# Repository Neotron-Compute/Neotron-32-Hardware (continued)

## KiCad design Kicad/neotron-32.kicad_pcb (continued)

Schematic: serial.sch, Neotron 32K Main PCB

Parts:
C901, C902: 100n; C_Disc_D3.0mm_W2.0mm_P2.50mm; mpn K104K15X7RF5TL2
C903, C904, C905: 100n; C_Disc_D3.0mm_W2.0mm_P2.50mm; mpn K474Z20Y5VE5TL2
J901: Conn_02x05; IDC-Header_2x05_P2.54mm_Vertical; mpn 302-S101
U901: ICL3232CPZMAX; DIP-16_W7.62mm; mpn ICL3232CPZ;ED16DT

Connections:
/PB0_U1RX: U901.12 (R1OUT); also elsewhere on the board
/PB1_U1TX: U901.11 (T1IN); also elsewhere on the board
/PC4_U1RTS: U901.10 (T2IN); also elsewhere on the board
/PC5_U1CTS: U901.9 (R2OUT); also elsewhere on the board
/RS-232 Serial Port/RS232_CTS_IN: J901.8, U901.8 (R2IN)
/RS-232 Serial Port/RS232_RTS_OUT: J901.7, U901.7 (T2OUT)
/RS-232 Serial Port/RS232_RX_IN: J901.2, U901.13 (R1IN)
/RS-232 Serial Port/RS232_TX_OUT: J901.3, U901.14 (T1OUT)
GND: C901.1, C904.1, J901.5, U901.15 (GND); also elsewhere on the board
unnamed: C902.1, U901.3 (C1-)
unnamed: C902.2, U901.1 (C1+)
unnamed: C903.1, U901.4 (C2+)
unnamed: C903.2, U901.5 (C2-)
unnamed: C904.2, U901.6 (VS-)
unnamed: C905.2, U901.2 (VS+)

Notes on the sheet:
Header for IDC to DE9 Ribbon. Wired DTE.
This chip is a 3.3V capable version of the MAX232 RS-232 level shifter. The port is wired DTE (i.e. as if this was an IBM PC, rather than as a modem). We only have a five-wire RS-232 interface, missing the Ring Input, Data Set Ready, Data Terminal Ready and Carrier Detect pins. If you want a proper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

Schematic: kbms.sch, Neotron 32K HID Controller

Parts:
C1002, C1003, C1004: 100n; C_Disc_D3.0mm_W2.0mm_P2.50mm; mpn K104K15X7RF5TL2
D1001, D1002: LED; LED_D3.0mm
FB1001: 100R; LairdTech_28C0236-0JW-10
J1002: 1x3 UART Debug Header; PinHeader_1x03_P2.54mm_Vertical
J1003: Double-mini-DIN-6; Double_mini-DIN_6; mpn KMDGX-6S-6S-S4N.
J1004: AVR-ISP-6; PinHeader_2x03_P2.54mm_Vertical
R1004, R1005: 1k; R_Axial_DIN0207_L6.3mm_D2.5mm_P10.16mm_Horizontal
R1006, R1008: 6.81k 1%; R_Axial_DIN0207_L6.3mm_D2.5mm_P10.16mm_Horizontal
R1007, R1009: 1k 1%; R_Axial_DIN0207_L6.3mm_D2.5mm_P10.16mm_Horizontal
R1010: 10k; R_Axial_DIN0207_L6.3mm_D2.5mm_P10.16mm_Horizontal
SW1001: SW_Push_DPDT_ON_MO; PHB2UEETS1A; mpn PHB2UOATS1A
U1002: ATmega328P-PU; DIP-28_W7.62mm

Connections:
+5V: C1003.1, FB1001.2, J1003.4, J1003.10, J1004.2 (VCC), R1004.1, R1005.1, R1006.2, U1002.7 (VCC); also elsewhere on the board
/Keyboard and Mouse/AT_MISO: J1004.1 (MISO), U1002.18 (PB4)
/Keyboard and Mouse/AT_MOSI: J1004.4 (MOSI), U1002.17 (PB3)
/Keyboard and Mouse/AT_SCK: J1004.3 (SCK), U1002.19 (PB5)
/Keyboard and Mouse/KB_CLK: J1003.5, U1002.4 (PD2)
/Keyboard and Mouse/KB_DAT: J1003.1, U1002.6 (PD4)
/Keyboard and Mouse/MON_3V3: R1008.1, R1009.2, U1002.24 (PC1)
/Keyboard and Mouse/MON_5V0: R1006.1, R1007.2, U1002.23 (PC0)
/Keyboard and Mouse/MS_CLK: J1003.11, U1002.5 (PD3)
/Keyboard and Mouse/MS_DAT: J1003.7, U1002.11 (PD5)
/Keyboard and Mouse/UART_RX: J1002.1, U1002.2 (PD0)
/Keyboard and Mouse/UART_TX: J1002.2, U1002.3 (PD1)
/Keyboard and Mouse/~AT_RESET: J1004.5 (~RST), U1002.1 (~RESET~/PC6)
/PA6_I2C_SCL: U1002.28 (PC5); also elsewhere on the board
/PA7_I2C_SDA: U1002.27 (PC4); also elsewhere on the board
/~PF4_HID_IRQ: U1002.26 (PC3); also elsewhere on the board
/~POWER_ON: R1010.1, U1002.25 (PC2); also elsewhere on the board
/~RESET: U1002.12 (PD6); also elsewhere on the board
GND: C1002.1, C1003.2, C1004.2, J1002.3, J1003.3, J1003.9, J1004.6 (GND), R1007.1, R1009.1, SW1001.2 (B), SW1001.5 (B), U1002.8 (GND), U1002.22 (GND); also elsewhere on the board
unnamed: C1002.2, U1002.21 (AREF)
unnamed: C1004.1, FB1001.1, U1002.20 (AVCC)
unnamed: D1001.1 (K), U1002.15 (PB1)
unnamed: D1001.2 (A), R1004.2
unnamed: D1002.1 (K), U1002.16 (PB2)
unnamed: D1002.2 (A), R1005.2
unnamed: R1010.2, SW1001.3 (C), SW1001.6 (C), U1002.13 (PD7)

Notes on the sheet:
The AtMega 328 acts as the interface to the 5V PS/2 Keyboard and PS/2 Mouse. It does this by implementing the Microsoft "HID over I2C" standard. The AtMega also handles the power button. When off, a short push will ground ~POWER_EN~, which will activate the PSU. Once the AtMega has booted it sets P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
Voltage Monitoring: measure against 1.1V band-gap ref (5.0V * 1000) / (6810 + 1000) = 640 mV (3.3V * 1000) / (6810 + 1000) = 422 mV
Power Button: Tap to turn on/off Hold to hard power off (if main MCU has crashed)
LEDs - Power and Fault
AtMega328 Pin Functions

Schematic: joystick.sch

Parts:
C1101: 100n; C_Disc_D3.0mm_W2.0mm_P2.50mm; mpn K104K15X7RF5TL2
J1101: 2x3 Header; PinHeader_2x03_P2.54mm_Vertical
R1101, R1102, R1103: 10k; R_Axial_DIN0207_L6.3mm_D2.5mm_P10.16mm_Horizontal
U1101: MCP23017_SP; DIP-28_W7.62mm

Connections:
+5V: C1101.1, J1101.1, J1101.3, J1101.5, U1101.9 (VDD); also elsewhere on the board
/Joystick/JS1_A_B: U1101.5 (GPB4); also elsewhere on the board
/Joystick/JS1_DOWN: U1101.2 (GPB1); also elsewhere on the board
/Joystick/JS1_LEFT: U1101.3 (GPB2); also elsewhere on the board
/Joystick/JS1_RIGHT: U1101.4 (GPB3); also elsewhere on the board
/Joystick/JS1_SELECT: U1101.7 (GPB6); also elsewhere on the board
/Joystick/JS1_START_C: U1101.6 (GPB5); also elsewhere on the board
/Joystick/JS1_UP: U1101.1 (GPB0); also elsewhere on the board
/Joystick/JS2_A_B: U1101.25 (GPA4); also elsewhere on the board
/Joystick/JS2_DOWN: U1101.22 (GPA1); also elsewhere on the board
/Joystick/JS2_LEFT: U1101.23 (GPA2); also elsewhere on the board
/Joystick/JS2_RIGHT: U1101.24 (GPA3); also elsewhere on the board
/Joystick/JS2_SELECT: U1101.27 (GPA6); also elsewhere on the board
/Joystick/JS2_START_C: U1101.26 (GPA5); also elsewhere on the board
/Joystick/JS2_UP: U1101.21 (GPA0); also elsewhere on the board
/PA6_I2C_SCL: U1101.12 (SCK); also elsewhere on the board
/PA7_I2C_SDA: U1101.13 (SDA); also elsewhere on the board
GND: C1101.2, R1101.1, R1102.1, R1103.1, U1101.10 (VSS); also elsewhere on the board
unnamed: J1101.2, R1101.2, U1101.17 (A2)
unnamed: J1101.4, R1102.2, U1101.16 (A1)
unnamed: J1101.6, R1103.2, U1101.15 (A0)

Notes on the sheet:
Address Select
The MCP23017 handles the two Atari/SEGA controller ports. A SEGA Master System pad is much like an Atari joystick, but a Mega Drive (or Genesis) 3-button pad will return both Left and Right active (low) when read. As this is impossible on a standard Joystick, this indicates it is a SEGA pad and tha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

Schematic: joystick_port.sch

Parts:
J1101: DE9 Male; DSUB-9_Male_Horizontal_P2.77x2.84mm_EdgePinOffset14.56mm_Ho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; mpn 5747467-2

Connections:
+5V: J1101.1, J1101.3, J1101.5; also elsewhere on the board
unnamed 118: J1101.2; also elsewhere on the board
unnamed 119: J1101.4; also elsewhere on the board
unnamed 120: J1101.6; also elsewhere on the board

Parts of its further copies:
J1201, J1301: DE9 Male; DSUB-9_Male_Horizontal_P2.77x2.84mm_EdgePinOffset14.56mm_Ho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; mpn 5747467-2

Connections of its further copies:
+5V: J1201.5, J1301.5; also elsewhere on the board
/Joystick/JS1_A_B: J1301.6; also elsewhere on the board
/Joystick/JS1_DOWN: J1301.2; also elsewhere on the board
/Joystick/JS1_LEFT: J1301.3; also elsewhere on the board
/Joystick/JS1_RIGHT: J1301.4; also elsewhere on the board
/Joystick/JS1_SELECT: J1301.7; also elsewhere on the board
/Joystick/JS1_START_C: J1301.9; also elsewhere on the board
/Joystick/JS1_UP: J1301.1; also elsewhere on the board
/Joystick/JS2_A_B: J1201.6; also elsewhere on the board
/Joystick/JS2_DOWN: J1201.2; also elsewhere on the board
/Joystick/JS2_LEFT: J1201.3; also elsewhere on the board
/Joystick/JS2_RIGHT: J1201.4; also elsewhere on the board
/Joystick/JS2_SELECT: J1201.7; also elsewhere on the board
/Joystick/JS2_START_C: J1201.9; also elsewhere on the board
/Joystick/JS2_UP: J1201.1; also elsewhere on the board
GND: J1201.8, J1301.8; also elsewhere on the board

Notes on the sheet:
Digital Atari/SEGA Compatible Joystick Port If LEFT and RIGHT read as GND, flip SELECT and read alternate set of pins (C, B, LEFT, RIGHT).

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
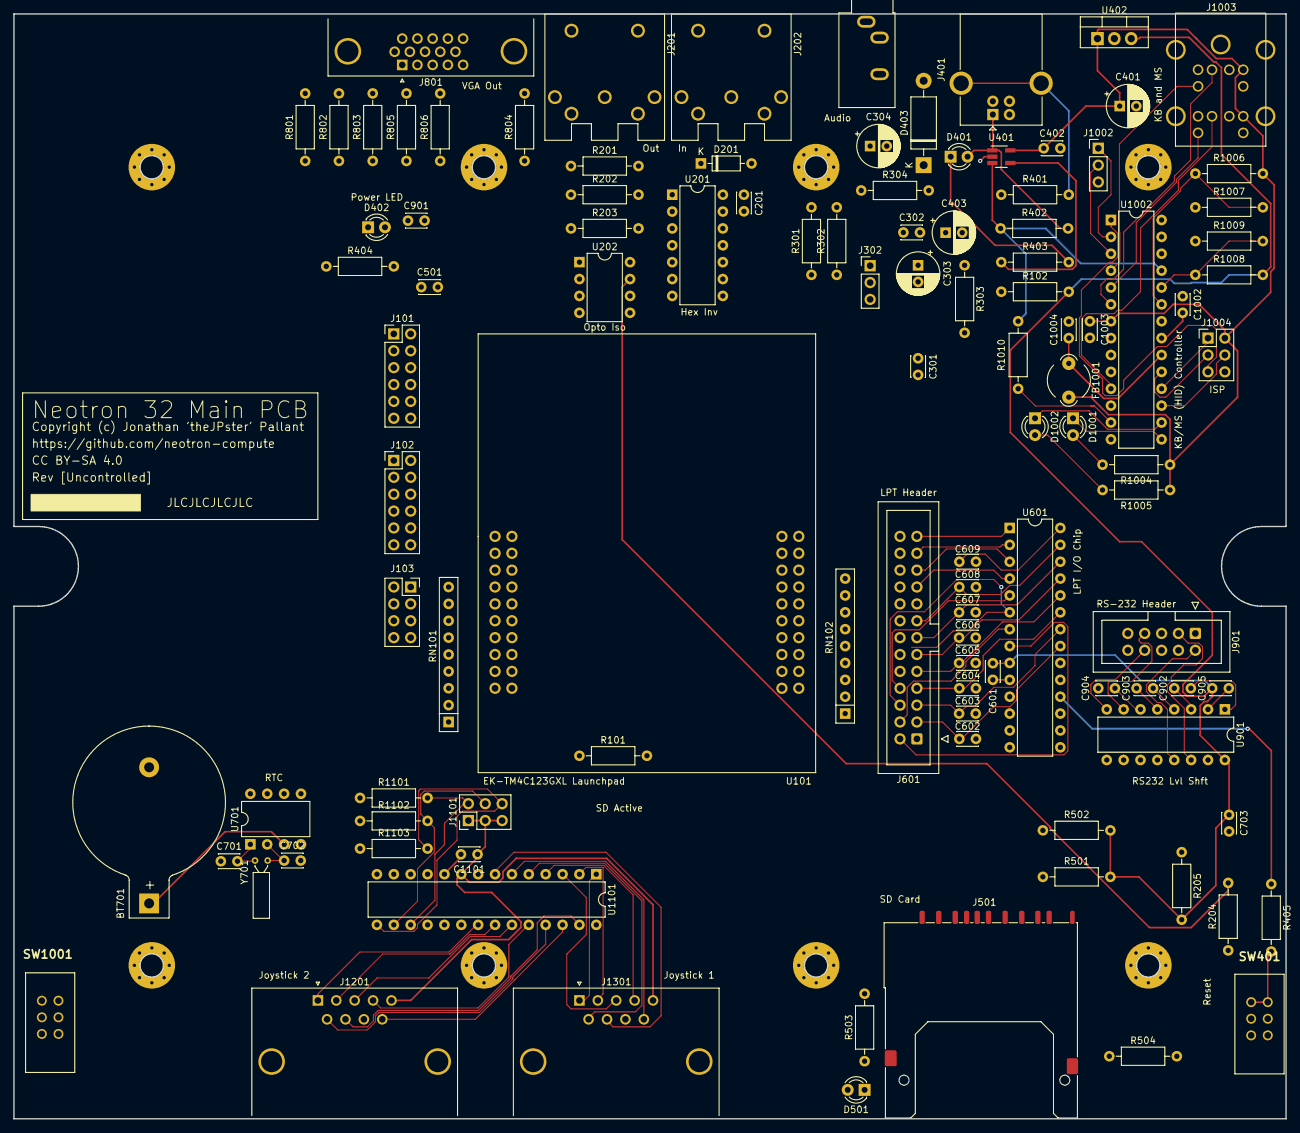
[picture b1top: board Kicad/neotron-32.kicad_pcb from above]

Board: 2 copper layers, 191.5 x 166.3 mm, 116 parts (0 on the bottom side), 130 nets.

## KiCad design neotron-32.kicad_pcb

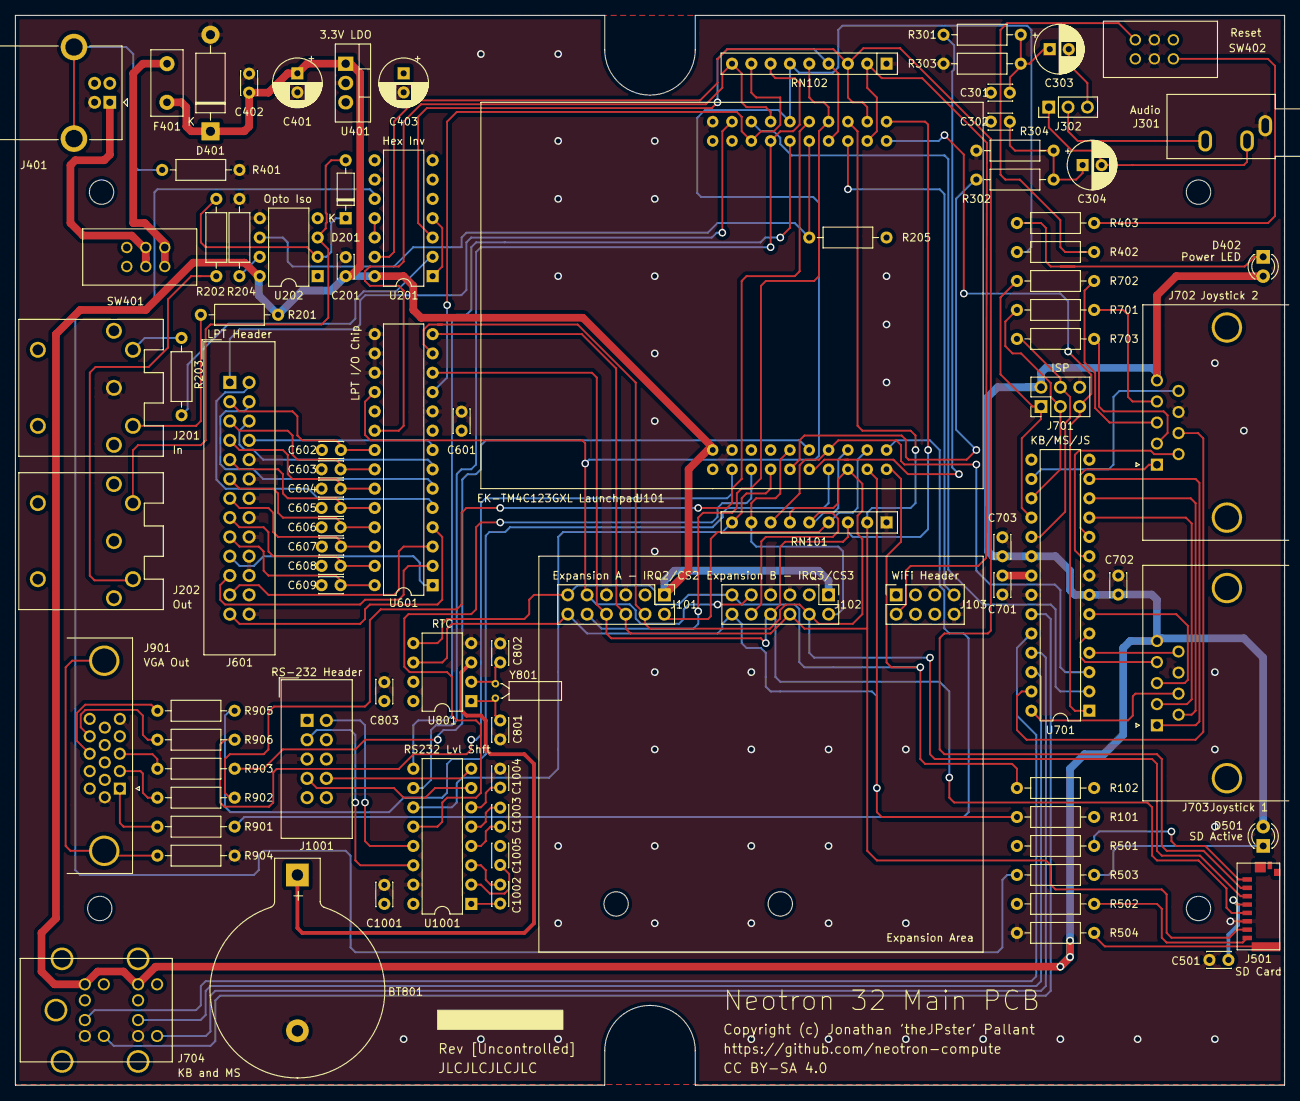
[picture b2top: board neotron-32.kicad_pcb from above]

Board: 4 copper layers, 166.9 x 140.7 mm, 97 parts (0 on the bottom side), 117 nets.

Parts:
BT801: CR2032; BatteryHolder_Keystone_103_1x20mm
C201, C402, C501, C601, C701, C702, C703, C803, C1001, C1002, C1003, C1004, C1005: 100n; C_Disc_D3.0mm_W2.0mm_P2.50mm
C301, C302: 33n; C_Disc_D3.0mm_W2.0mm_P2.50mm
C303, C304, C401: 10u; CP_Radial_D6.3mm_P2.50mm
C403: 47u; CP_Radial_D6.3mm_P2.50mm
C602, C603, C604, C605, C606, C607, C608, C609: 22n; C_Disc_D3.0mm_W2.0mm_P2.50mm
C801, C802: 6p; C_Disc_D3.0mm_W2.0mm_P2.50mm
D201: 1N4148; D_DO-35_SOD27_P7.62mm_Horizontal
D401: SA5.0A; D_DO-15_P12.70mm_Horizontal
D402, D501: Red LED; LED_D3.0mm
F401: 250mA PTC; Fuse_Littelfuse_395Series
H101, H102, H103, H104, H105, H106: MountingHole; MountingHole_3.2mm_M3
J101, J102: Conn_02x06; PinHeader_2x06_P2.54mm_Vertical
J103: Conn_02x04; PinSocket_2x04_P2.54mm_Vertical
J201, J202: DIN-5 180 degree; 5P180_DIN_Socket
J301: 3.5mm Audio Jack TRS; Jack_3.5mm_CUI_SJ1-3533NG_Horizontal
J302: Conn_01x03_Male; PinHeader_1x03_P2.54mm_Vertical
J401: USB_B; USB_B_OST_USB-B1HSxx_Horizontal
J501: micro SD Card; Molex_4730_2651
J601: Conn_02x13_Header; IDC-Header_2x13_P2.54mm_Vertical
J701: AVR-ISP-6; PinHeader_2x03_P2.54mm_Vertical
J702, J703: DE9 Male; DSUB-9_Male_Horizontal_P2.77x2.84mm_EdgePinOffset14.56mm_Ho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
J704: Double-mini-DIN-6; Double_mini-DIN_6
J901: DB15HD_Female; DSUB-15-HD_Female_Horizontal_P2.29x1.98mm_EdgePinOffset3.03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
J1001: Conn_02x05; IDC-Header_2x05_P2.54mm_Vertical
R101, R102, R701, R702, R703: 1k; R_Axial_DIN0207_L6.3mm_D2.5mm_P10.16mm_Horizontal
R201, R202, R203: 220; R_Axial_DIN0207_L6.3mm_D2.5mm_P10.16mm_Horizontal
R204: 10k; R_Axial_DIN0207_L6.3mm_D2.5mm_P10.16mm_Horizontal
R205: 470; R_Axial_DIN0207_L6.3mm_D2.5mm_P10.16mm_Horizontal
R301, R302: 270; R_Axial_DIN0207_L6.3mm_D2.5mm_P10.16mm_Horizontal
R303, R304: 150; R_Axial_DIN0207_L6.3mm_D2.5mm_P10.16mm_Horizontal
R401, R504, R904: DNF; R_Axial_DIN0207_L6.3mm_D2.5mm_P10.16mm_Horizontal
R402, R403, R503, R901, R902, R903, R905, R906: 330; R_Axial_DIN0207_L6.3mm_D2.5mm_P10.16mm_Horizontal
R501, R502: 47k; R_Axial_DIN0207_L6.3mm_D2.5mm_P10.16mm_Horizontal
RN101, RN102: 47k x 8; R_Array_SIP9
SW401: SW_Push_DPDT_ON_OFF; PHB2UEETS1A
SW402: SW_Push_DPDT_ON_MO; PHB2UEETS1A
U101: EK-TM4C123GXL; Launchpad_4x10
U201: 74LS14; DIP-14_W7.62mm
U202: 6N138; DIP-8_W7.62mm
U401: TC1262-33; TO-220-3_Vertical
U601: MCP23S17_SP; DIP-28_W7.62mm
U701: ATmega328-PU; DIP-28_W7.62mm
U801: MCP7940N-xP; DIP-8_W7.62mm
U1001: ICL3232CPZMAX; DIP-16_W7.62mm
Y801: 32,768 Hz; Crystal_C26-LF_D2.1mm_L6.5mm_Horizontal

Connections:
+3V3: C403.1, C501.1, C601.1, C803.1, C1001.2, C1005.1, J101.3, J102.3, J103.1, J501.4, R101.2, R102.2, R205.2, R501.2, R502.2, U401.3, U601.9, U801.8, U1001.16
+5V: C201.1, C401.1, C402.1, C702.1, C703.1, D401.1, D402.2, D501.2, F401.1, J101.1, J102.1, J701.2, J702.5, J703.5, J704.4, J704.10, R201.2, U101.3.1, U201.14, U202.8, U401.1, U701.7, U701.20
+BATT: BT801.1, U801.3
/Audio/LEFT_CHAN: C304.2, J301.T, J302.1
/Audio/RIGHT_CHAN: C303.2, J302.3
/Audio/RIGHT_SPKR: J301.R, J302.2
/Keyboard, Mouse and Joystick/AT_MISO: J701.1, R702.2, U701.18
/Keyboard, Mouse and Joystick/AT_MOSI: J701.4, R703.2, U701.19
/Keyboard, Mouse and Joystick/AT_SCK: J701.3, R701.2, U701.17
/Keyboard, Mouse and Joystick/A_B_JS1: J703.6, U701.12
/Keyboard, Mouse and Joystick/A_B_JS2: J702.6, U701.9
/Keyboard, Mouse and Joystick/DOWN_JS1: J703.2, U701.11
/Keyboard, Mouse and Joystick/DOWN_JS2: J702.2, R703.1
/Keyboard, Mouse and Joystick/KB_CLK: J704.5, U701.23
/Keyboard, Mouse and Joystick/KB_DAT: J704.1, U701.24
/Keyboard, Mouse and Joystick/LEFT_GND_JS1: J703.3, U701.6
/Keyboard, Mouse and Joystick/LEFT_GND_JS2: J702.3, R702.1
/Keyboard, Mouse and Joystick/MS_CLK: J704.11, U701.25
/Keyboard, Mouse and Joystick/MS_DAT: J704.7, U701.26
/Keyboard, Mouse and Joystick/RIGHT_GND_JS1: J703.4, U701.5
/Keyboard, Mouse and Joystick/RIGHT_GND_JS2: J702.4, R701.1
/Keyboard, Mouse and Joystick/SELECT_JS1: J703.7, U701.28
/Keyboard, Mouse and Joystick/SELECT_JS2: J702.7, U701.27
/Keyboard, Mouse and Joystick/START_C_JS1: J703.9, U701.4
/Keyboard, Mouse and Joystick/START_C_JS2: J702.9, U701.16
/Keyboard, Mouse and Joystick/UP_JS1: J703.1, U701.13
/Keyboard, Mouse and Joystick/UP_JS2: J702.1, U701.10
/PA2_SPI_CLK: J101.8, J102.8, J501.5, RN101.3, U101.2.10, U601.12
/PA4_SPI_MISO: J101.6, J102.6, J501.7, RN101.2, U101.2.8, U601.14
/PA5_SPI_MOSI: J101.4, J102.4, J501.3, RN101.6, U101.1.8, U601.13
/PA6_I2C_SCL: J101.12, J102.12, R101.1, U101.1.9, U801.6
/PA7_I2C_SDA: J101.11, J102.11, R102.1, U101.1.10, U801.5
/PB0_U1RX: U101.1.3, U1001.12
/PB1_U1TX: RN101.9, U101.1.4, U1001.11
/PB4_VGA_HSYNC: R905.1, U101.1.7
/PB5_VGA_VSYNC: R906.1, U101.1.2
/PB7_VGA_GREEN: R902.2, U101.2.6
/PC4_U1RTS: RN102.7, U101.4.4, U1001.10
/PC5_U1CTS: U101.4.5, U1001.9
/PC6_MIDI_IN: R205.1, U101.4.6, U202.6
/PC7_MIDI_OUT: RN102.4, U101.4.7, U201.3
/PD3_VGA_BLUE: R903.2, U101.3.6
/PD6_U2RX: J103.7, U101.4.8
/PD7_U2TX: J103.2, RN102.2, U101.4.9
/PE0_U7RX: U101.2.3, U701.2
/PE1_U7TX: RN101.7, U101.3.7, U701.3
/PE4_AUDIO_L: R302.2, U101.1.5
/PE5_AUDIO_R: R301.2, U101.1.6
/PF1_VGA_RED: R901.2, U101.3.10
/Parallel Printer/ACK: J601.19, U601.1
/Parallel Printer/D0: C602.2, J601.3, U601.21
/Parallel Printer/D1: C603.2, J601.5, U601.22
/Parallel Printer/D2: C604.2, J601.7, U601.23
/Parallel Printer/D3: C605.2, J601.9, U601.24
/Parallel Printer/D4: C606.2, J601.11, U601.25
/Parallel Printer/D5: C607.2, J601.13, U601.26
/Parallel Printer/D6: C608.2, J601.15, U601.27
/Parallel Printer/D7: C609.2, J601.17, U601.28
/Parallel Printer/ERROR: J601.4, U601.6
/Parallel Printer/POUT: J601.23, U601.3
/Parallel Printer/RESET: J601.6, U601.7
/Parallel Printer/SELECT: J601.25, U601.4
/Parallel Printer/~BUSY: J601.21, U601.2
/Parallel Printer/~LF: J601.2, U601.5
/Parallel Printer/~SELPRI: J601.8, U601.8
/Power/UNFUSED_5V: F401.2, SW401.3, SW401.6
/Power/VUSB: J401.1, SW401.2, SW401.5
/RS-232 Serial Port/RS232_CTS_IN: J1001.8, U1001.8
/RS-232 Serial Port/RS232_RTS_OUT: J1001.7, U1001.7
/RS-232 Serial Port/RS232_RX_IN: J1001.2, U1001.13
/RS-232 Serial Port/RS232_TX_OUT: J1001.3, U1001.14
/~PA3_SPI_CS0: J501.2, RN102.3, U101.2.9, U201.13
/~PB2_STROBE: J601.1, U101.2.2
/~PB3_SPI_CS1: RN102.8, U101.4.3, U601.11
/~PB6_SPI_CS2: J101.10, RN102.5, U101.2.7
/~PD2_IRQ3: J102.2, RN101.8, U101.3.5
/~PE2_SPI_CS3: J102.10, RN101.5, U101.3.8
/~PE3_IRQ2: J101.2, RN101.4, U101.3.9
/~PF0_IRQ1: RN102.9, U101.2.4, U601.20
/~PF4_AT_RESET: J701.5, U101.4.10, U701.1
/~RESET: J101.9, J102.9, R402.1, RN102.6, U101.2.5, U601.18
GND: BT801.2, C201.2, C301.1, C302.1, C401.2, C402.2, C403.2, C501.2, C601.2, C602.1, C603.1, C604.1, C605.1, C606.1, C607.1, C608.1, C609.1, C701.1, C702.2, C703.2, C801.1, C802.2, C803.2, C1001.1, C1004.1, D401.2, J101.5, J101.7, J102.5, J102.7, J103.8, J201.2, J301.S, J401.4, J501.6, J601.10, J601.12, J601.14, J601.16, J601.18, J601.20, J601.22, J601.24, J601.26, J701.6, J702.8, J703.8, J704.3, J704.9, J901.5, J901.6, J901.7, J901.8, J1001.5, R204.1, R303.2, R304.2, R401.1, R504.2, R904.1, RN101.1, RN102.1, SW402.2, SW402.5, U101.2.1, U101.3.2, U201.5, U201.7, U201.9, U202.5, U401.2, U601.10, U601.15, U601.16, U601.17, U701.8, U701.22, U801.4, U1001.15
unnamed: C301.2, C303.1, R301.1, R303.1
unnamed: C302.2, C304.1, R302.1, R304.1
unnamed: C701.2, U701.21
unnamed: C801.2, U801.1, Y801.1
unnamed: C802.1, U801.2, Y801.2
unnamed: C1002.1, U1001.3
unnamed: C1002.2, U1001.1
unnamed: C1003.1, U1001.4
unnamed: C1003.2, U1001.5
unnamed: C1004.2, U1001.6
unnamed: C1005.2, U1001.2
unnamed: D201.1, R202.1, U202.2
unnamed: D201.2, J202.5, U202.3
unnamed: D402.1, R403.1
unnamed: D501.1, R503.1
unnamed: J201.4, R201.1
unnamed: J201.5, R203.2
unnamed: J202.4, R202.2
unnamed: J401.5, R401.2
unnamed: J501.1, R501.1
unnamed: J501.8, R502.1
unnamed: J501.9, R504.1
unnamed: J901.0, R904.2
unnamed: J901.1, R901.1
unnamed: J901.2, R902.1
unnamed: J901.3, R903.1
unnamed: J901.13, R905.2
unnamed: J901.14, R906.2
unnamed: R203.1, U201.2
unnamed: R204.2, U202.7
unnamed: R402.2, SW402.3
unnamed: R403.2, SW402.4
unnamed: R503.2, U201.10
unnamed: U201.1, U201.4
unnamed: U201.11, U201.12

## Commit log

2019-11-10 Skeleton schematic.
2019-11-10 Add datasheets and example schematics.
2019-11-10 Add USB Library user guide.
2019-12-08 Update hardware specs in README.
2019-12-09 Adding sub-sheets
2019-12-09 Ignore backup PCB files.
2019-12-09 Added some footprints. Basic board outline.
2019-12-10 Completed Power, SD, MIDI, Parallel and Joystick sheets.
    Switch to sheet based 100x part numbering.
2019-12-10 Add MCP23S17 data sheet.
2019-12-15 Schematic capture draft complete.
2019-12-15 Add github action file.
2019-12-15 Fix action syntax.
2019-12-15 Fix action paths.
2019-12-15 Where are my files?
2019-12-15 Testing actions
2019-12-16 Removing workflow, as it's broken.
2019-12-16 Tidied up Atmega power. Added page titles.
2019-12-17 Work in progress.
2019-12-19 Updated footprints: ) Swapped RS-232 DE9 for IDC header. ) Large caps are radial electrolytics. ) Made resistors a little smaller.
2019-12-19 Laid out components. Tracking partially complete.
2019-12-19 First draft layout complete. Fixing DRC issues.
2019-12-19 Layout first draft complete - passes DRC.
    Still need to nudge a few traces on to the grid.
    Also need to move all the silkscreen labels into place.
2019-12-19 Tidied some more tracks.
2019-12-20 Finished layout and silkscreen.
2019-12-20 Labelling as v0.7.0.
2019-12-20 Update rescue library
2019-12-21 Set version to [Uncontrolled].
    Replace [Uncontrolled] with actual revision in each release branch.
2019-12-21 Replace two PS/2 headers with single double-header.
2019-12-21 Replaced keyboard/mouse connect with double PS/2 header.
    Jiggled around PCB layout to line more tracks up on grid.
2019-12-21 Tagging sheets as v0.8.0
2019-12-21 Added double-DIN header to rescue lib.
2019-12-21 Replaced broken Keystone 103 footprint with edited one.
    Stops annoying DRC error.
2019-12-21 Resolve last two DRC errors: ) use updated battery holder ) fix clearance on SD card
2019-12-21 Added release building script.
2019-12-21 Fixed up release script to move/rename files into separate dir.
2019-12-21 Only emit certain layers as PCB PDF.
2019-12-21 Update README.
    ) Specify license is CC BY-SA 4.0.
    ) Note we have Serial and Parallel on headers.
    ) Note we support MS-DOS partitions
2019-12-22 Adding MPNs.
2019-12-22 Adding end panel drawing and top-level BOM.
    Also adding notes to keep track of progress.
2019-12-23 Nudge sockets around, and switch to LibreCAD for end panels.
    End panel needs more work.
2019-12-23 Add Hammond datasheet.
2019-12-23 Ignore more temporary files.
2019-12-23 Fix MIDI Out/Through mix-up.
2019-12-23 Removing MIDI Through.
2019-12-24 Re-laid out Joystick, MIDI and VGA.
    Re-worked Joystick connectors (were changed from Female to Male).
    Deleted MIDI Through.
    Moved up VGA connector.
2019-12-24 Update notes.
2019-12-24 Re-saved PCB.
2019-12-25 Windows Kicad produces different backup filenames.
2019-12-25 Use offset DE9 for Joysticks.
2019-12-25 Updated PCB layout:
    ) Moved Joystick ports inwards.
    ) Moved USB power connector inwards.
    ) Added copper pour on top layer.
2019-12-25 Updated schematic on Windows.
2019-12-25 Updated BOM.
2019-12-25 Rotated SD card.
2019-12-25 Removed Digikey and RS part numbers.
2019-12-26 Note in the README that it's a full-size SD card.
2019-12-26 Refill zones on Linux Kicad to avoid issues running release script.
2019-12-26 Ensure schematic PDF contains all of the pages.
2019-12-26 Add some extra explanatory notes.
2019-12-26 Set version.
2019-12-27 Fixed up end panel to match current PCB.
2019-12-27 Fix Stackpole 1K part number.
2019-12-27 Add link to Octopart BOM.
2019-12-27 Add Tindie link.
2019-12-27 Add metadata to silkscreen.
2019-12-27 Set revision at 0.9.1
2019-12-27 Ensure all layers go into Gerber file as some were missing.
2019-12-27 Updated NOTES.
2019-12-27 Add USB 3D model - using compatible TE part.
2019-12-27 Add PS/2 connector model.
2019-12-28 Add some more 3D models. Also add a 3D render to the README.
2019-12-28 PCB Updates.
    ) Moved SD LED next to SD card (makes space for future USB port)
    ) Set up Net Class for power tracks
    ) Set all power tracks to 0.5mm (suitable for up to 1A) - 1mm tracks were overkill
2019-12-29 Rotate drive activity LED. Tidy up bottom layer traces.
2020-01-03 Replace Amphenol SD connector with Molex.
    The Molex connector has the pins at the rear, which means you can blob
    down solder without fouling the card insertion.
2020-01-03 Move VGA connector in to align with PCB edge.
2020-01-03 Remove unused datasheet.
2020-01-03 Remove yet another hole in the flood fill, near the Exp connectors.
2020-01-04 Moved non-standard components into local libraries.
    neotron-32.lib is the symbol library.
    neotron-32.pretty is the footprint library.
    Also swapped the DE9 and DB25 headers for IDC boxed versions. Involved
    moving a resistor out of the way.
    The Keystone 103 battery holder is a straight copy of the standard
    footprint, but with the Courtyard removed to bypass the 'Courtyard is
2020-01-04 Add a push button power switch.
    Also moved reset into the corner and tidied up a few tracks.
2020-01-04 Fixed spacing between MIDI connectors.
    Also tidied up some more tracks and re-aligned end panel.
2020-01-05 Added Reset switch.
    Also added 3D models.
2020-01-05 Restore endpanel drawing.
    Not sure how the drawing was lost, but hurrah for git!
2020-01-05 Set version to v1.0.0
2020-01-05 Set output format to Gebers and PDF.
2020-01-05 Update rescue lib.
2020-01-05 Enable all layers in Gerber output.
2020-01-06 Moved some tracks away from the Neotron silkscreen text.
    Also removed some weird trace overlaps near the Wifi connector.
2020-01-06 Only plot relevant layers.
2020-01-06 Laying out board again, but on a 50 mil grid for parts.
    Will use 25 mil grid for traces. This will hopefully avoid the issue
    of traces 'sticking' to legs rather than cleanly going precisely down
    the middle. It also looks a lot nicer now everything is properly
    aligned.
    I've also taken the opportunity to put the expansion slots all next to each other.
    Might need to add some support holes for some legs, a la M.2 SSDs.
2020-01-09 Added some more tracks.
2020-01-13 Work tracing done.
2020-01-14 More tracking.
2020-01-15 WIP on 4 layer.
    It's much easier than the two layer board!
2020-01-16 Completed tracking. Just needs a tidy.
2020-01-16 Tidied up layout a bit. Also ensured all four layers in release.sh.
2020-01-16 Join VGA GND together.
2020-01-17 Manhattan, not diagonals.
    Aligning tracks on north/south and east/west is more
    visually pleasing than taking the diagonal. Having to fight the autorouter
    a bit though. In an ideal work we'd have north/south on one layer
    and east/west on the other, but meh.
2020-01-18 Swapped Wifi pin header for socket.
2020-01-18 Swapped WiFi pin header for socket. Removed 5V from 3.3V plane.
2020-01-18 More de-diagonalisation.
2020-01-18 Remove old layout
2020-01-19 Fixed footprints.
    ) Parallel port was wrongly numbered.
    ) Input fuse has 0.2" leg spacing.
    ) Also cleaned up a few more diagonals.
2020-01-19 Add RTC data sheet.
2020-01-19 Add missing datasheets.
2020-01-19 Adding new component to rescue library.
2020-01-19 Last of the diagonals abolished.
2020-01-19 Setting version to v1.2.0
2020-01-19 Adding alternative kicad-automation Makefile.
    See https://github.com/obra/kicad-tools
2020-01-19 Updated endpanel using photo.
2020-01-19 Adding photo of end-on view.
2020-01-20 Enable bottom mask.
2020-01-20 Tagging as v1.2.1.
    Same as v1.2.0 but has bottom solder mask enabled.
2020-01-30 Added new pictures, and details of software required.
2020-03-29 Bug fixes part 1.
    * Added XTAL to Atmega.
    * Added UART header to Atmega.
    * Added page numbers.
    * Removed the 470R in favour of 330R (to rationalise the BOM)
    * Replaced MAX3232 caps with 100n
2020-04-22 Added Atmega PDF.
2020-05-31 Replace PartNum with MPN so Kicost can see it.
2020-05-31 Tweaks to the BOM.
    Marking parts as DNP=1 should stop them appearing in the BOM.
    Also set multi-parts for ICs in sockets.
2020-06-01 Add some Digikey part numbers.
2020-06-01 Add kitspace file.
2020-06-01 Update README.
    Mention OpenHardware. Remove Tindie link.
2020-06-01 Add BOM for kitspace
2020-06-02 Cleaned up Atmega reset. Set hold size to 3.5mm, so M3 screws go through nicely Reset numbering to page x 100 Renamed Launchpad to EK-TM4C123GXL Renamed top-level signals to KBMS page as KBMS_TO/FROM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
2020-06-02 Shift power and reset inwards. Add ground fill top/bottom.
2020-06-03 Added link to main site.
2020-06-04 Update BOM from Kicad.
    Exported with bom2grouped_csv.
2020-06-04 Rebuild BOM with new part numbers.
2020-06-04 Add link to Kitspace and new Octopart BOM.
2020-06-04 Fix #21 and #25.
2020-06-12 Moving Kicad stuff into Kicad sub-folder.
2020-06-13 Kicad files moved into Kicad folder.
2020-06-13 Deleted DNP parts, and added Digikey part numbers.
2020-06-13 Clean up BOM - add friendlier part descriptions.
2020-06-13 Change Harwin 12-pin header part number.
2020-08-19 Ignore backup files.
2020-08-19 Switch to 1598D enclosure.
    Use MIC2005A current limiter on input.
    Use soft on/off switch from Atmega.
    Atmega connects to Tiva over I2C.
    Use full-size SD card.
2020-08-20 Working on layout.
    Laid out the parallel port - reordered some pins to make it easier.
    Set the minimum track widths to 6 mil/6 mil with a 6mm/3mm via.
    Replaced the SPST power switch with a PUE to match the reset switch.
    Attached some existing 3D models to the PCB footprints.
2020-08-21 Moved Joystick controller onto its own sheet.
2020-09-05 Ignore bck files
2020-09-05 Fixed up path to 3D models.
    Also tidied up a few tracks to get better top pour.
